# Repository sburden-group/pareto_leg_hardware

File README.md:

# Pareto Leg Hardware

contains all hardware (and control software) designs for the Pareto Leg

## Setup
Getting your environment ready to talk to some robot legs will involve:
1. provisioning your computer
1. provisioning the ODrive with the right firmware
1. calibrating the ODrive motors
1. Assembling the leg hardware
1. Wiring the leg electronics
1. Setting the zero point for each leg element

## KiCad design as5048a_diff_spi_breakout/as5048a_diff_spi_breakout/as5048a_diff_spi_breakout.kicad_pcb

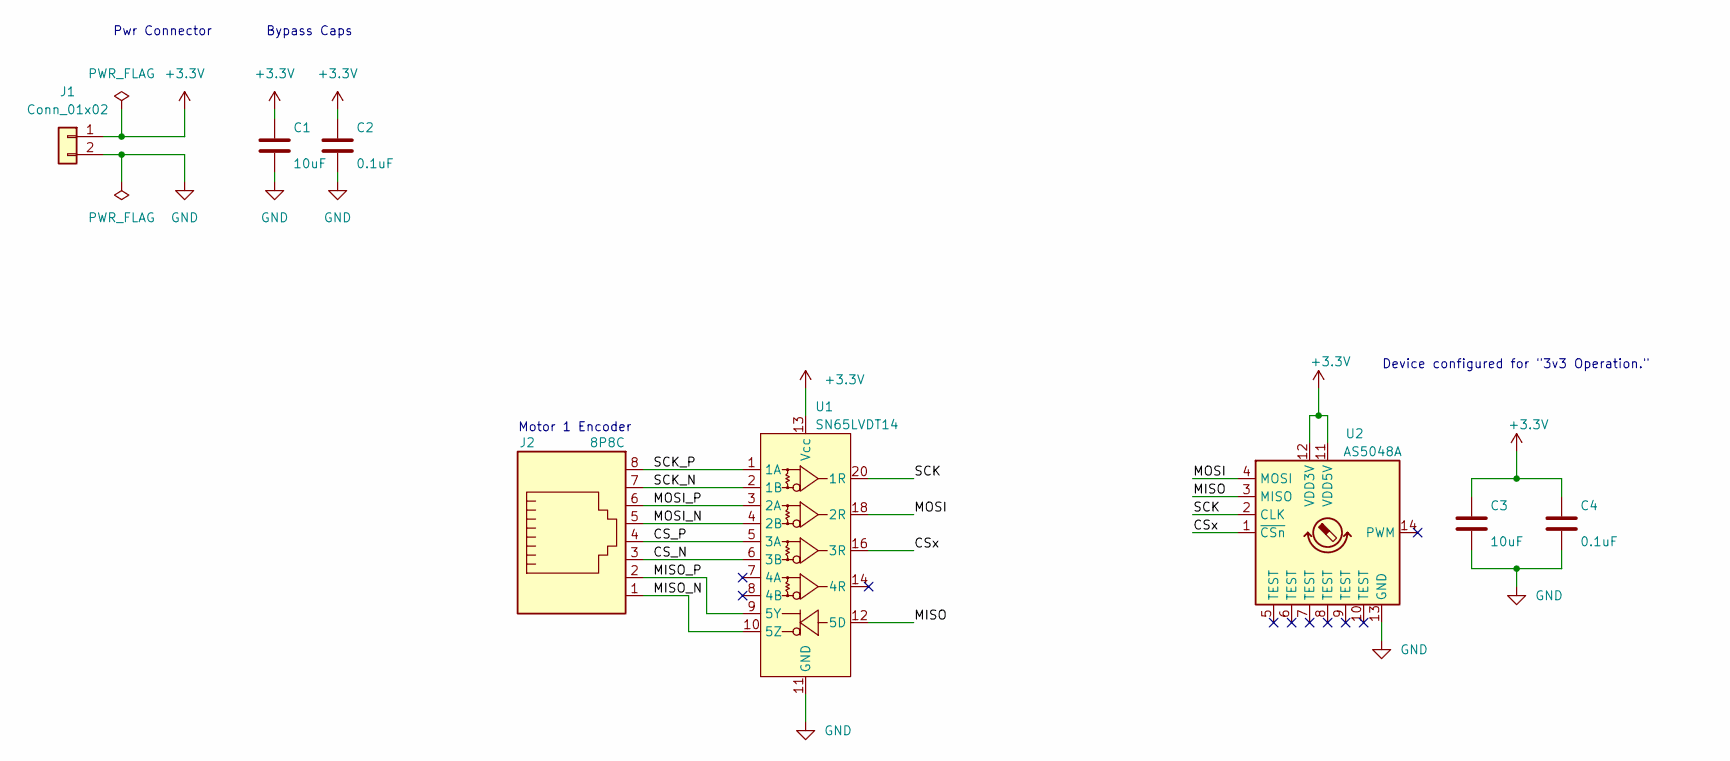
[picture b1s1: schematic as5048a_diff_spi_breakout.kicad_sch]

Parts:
C1, C3: 10uF; C_0603_1608Metric_Pad1.05x0.95mm_HandSolder
C2, C4: 0.1uF; C_0603_1608Metric_Pad1.05x0.95mm_HandSolder
J1: Conn_01x02; Molex_Micro-Fit_3.0_43650-0212_1x02_P3.00mm
J2: 8P8C; RJ45_Amphenol_SMD_RJSSE-5080-01T
U1: SN65LVDT14; TSSOP-20_4.4x6.5mm_P0.65mm
U2: AS5048A; TSSOP-14_4.4x5mm_P0.65mm

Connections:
+3V3: C1.1, C2.1, C3.1, C4.1, J1.1, U1.13 (Vcc), U1.17 (Vcc), U2.11 (VDD5V), U2.12 (VDD3V)
/CS_N: J2.3, U1.6 (3B)
/CS_P: J2.4, U1.5 (3A)
/CSx: U1.16 (3R), U2.1 (~CSn)
/MISO: U1.12 (5D), U2.3 (MISO)
/MISO_N: J2.1, U1.10 (5Z)
/MISO_P: J2.2, U1.9 (5Y)
/MOSI: U1.18 (2R), U2.4 (MOSI)
/MOSI_N: J2.5, U1.4 (2B)
/MOSI_P: J2.6, U1.3 (2A)
/SCK: U1.20 (1R), U2.2 (CLK)
/SCK_N: J2.7, U1.2 (1B)
/SCK_P: J2.8, U1.1 (1A)
GND: C1.2, C2.2, C3.2, C4.2, J1.2, U1.11 (GND), U1.15 (GND), U1.19 (GND), U2.13 (GND)

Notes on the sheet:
Pwr Connector
Motor 1 Encoder
Bypass Caps
Device configured for "3v3 Operation."

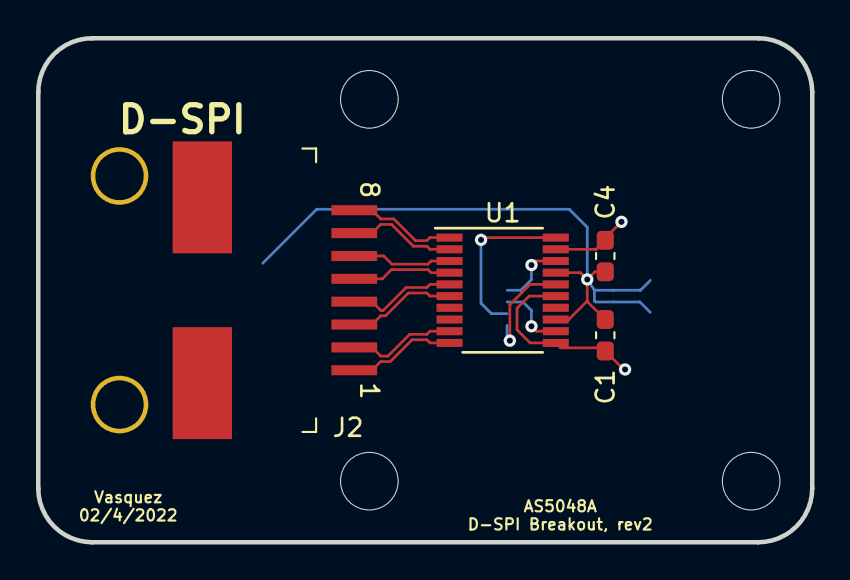
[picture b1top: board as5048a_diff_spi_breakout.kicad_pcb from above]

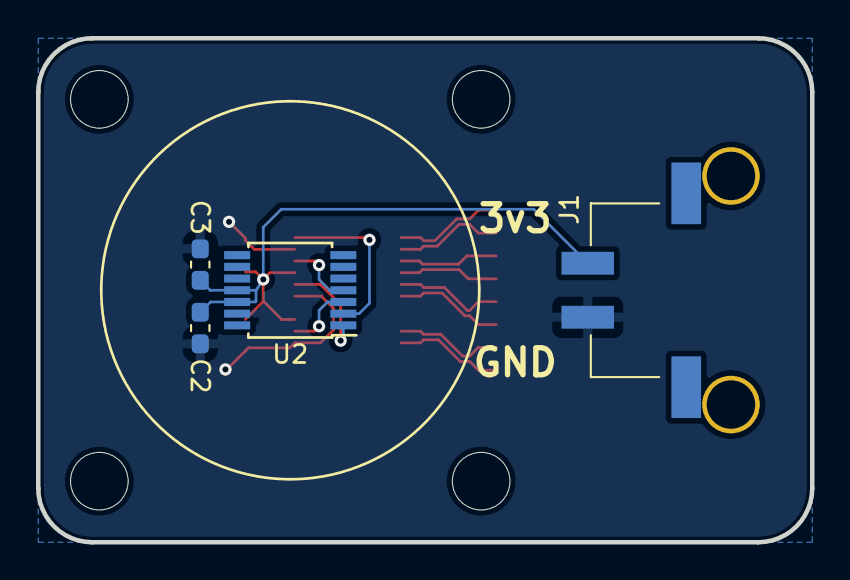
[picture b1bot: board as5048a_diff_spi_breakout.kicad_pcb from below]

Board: 2 copper layers, 43.0 x 28.0 mm, 8 parts (4 on the bottom side), 14 nets.

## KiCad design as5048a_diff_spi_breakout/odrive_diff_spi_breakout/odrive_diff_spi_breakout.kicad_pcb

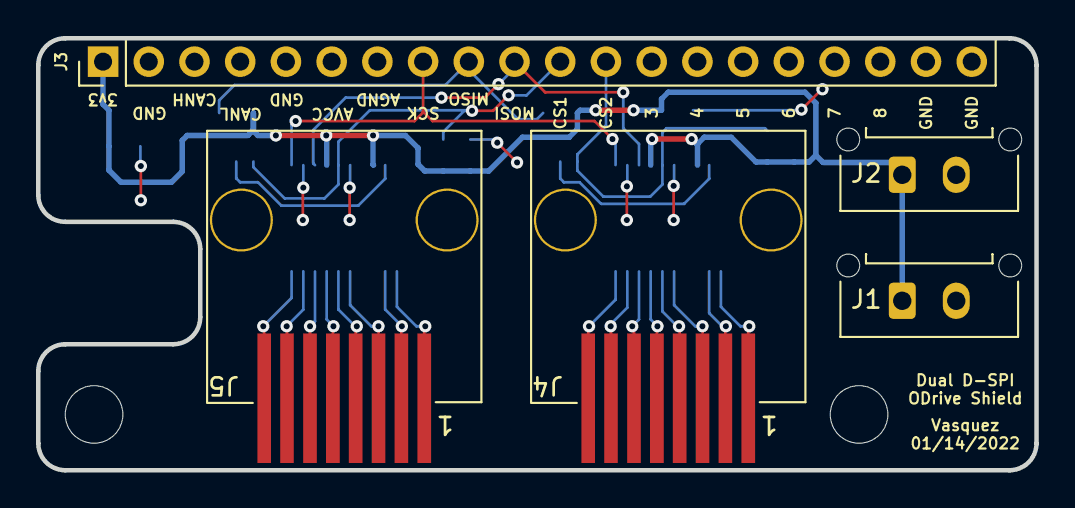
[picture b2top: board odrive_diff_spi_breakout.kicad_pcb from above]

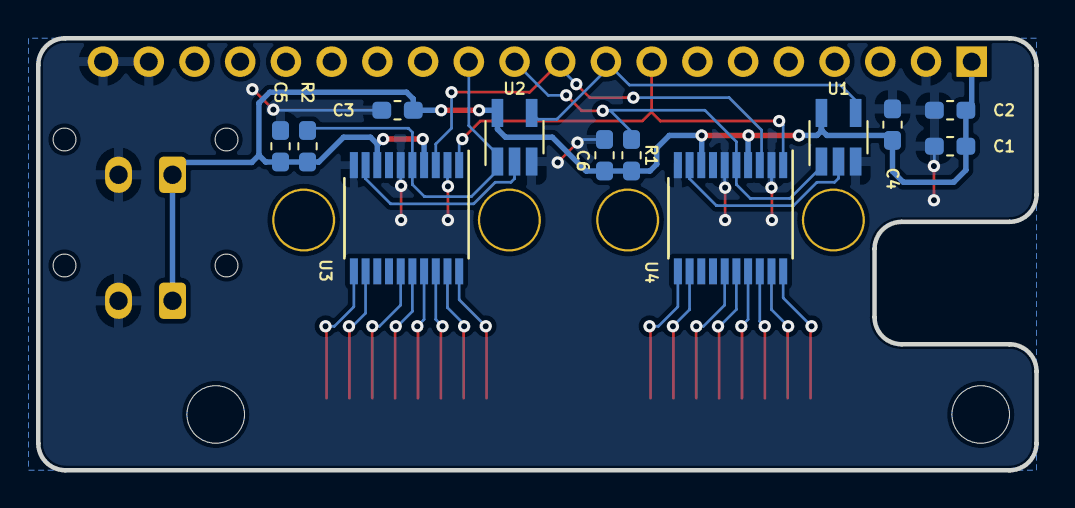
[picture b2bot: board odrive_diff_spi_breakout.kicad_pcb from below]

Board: 2 copper layers, 55.5 x 24.0 mm, 17 parts (12 on the bottom side), 25 nets.

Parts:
C1: 10uF; C_0603_1608Metric_Pad1.05x0.95mm_HandSolder
C2, C3, C4: 0.1uF; C_0603_1608Metric_Pad1.05x0.95mm_HandSolder
C5, C6: 1uF; C_0603_1608Metric_Pad1.05x0.95mm_HandSolder
J1, J2: Conn_01x02; Molex_Micro-Fit_3.0_43650-0215_1x02_P3.00mm_Vertical
J3: Conn_01x20; PinHeader_1x20_P2.54mm_Vertical
J4, J5: 8P8C; RJ45_Molex_SMD_0955036891
R1, R2: 4k7; R_0603_1608Metric_Pad1.05x0.95mm_HandSolder
U1, U2: 74CBTLV1G125; SOT-23-5_HandSoldering
U3, U4: SN65LVDT41; TSSOP-20_4.4x6.5mm_P0.65mm

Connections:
+3V3: C1.1, C2.1, C3.1, C4.1, C5.1, C6.1, J1.1, J2.1, J3.1, R1.1, R2.1, U1.5 (VCC), U2.5 (VCC), U3.4 (Vcc), U3.8 (Vcc), U4.4 (Vcc), U4.8 (Vcc)
/CS1: J3.11, R1.2, U1.1 (~OE), U4.5 (3D)
/CS2: J3.12, R2.2, U2.1 (~OE), U3.5 (3D)
/MISO: J3.9, U1.4 (B), U2.4 (B)
/MISO1: U1.2 (A), U4.9 (5R)
/MISO2: U2.2 (A), U3.9 (5R)
/MOSI: J3.10, U3.3 (2D), U4.3 (2D)
/SCK: J3.8, U3.1 (1D), U4.1 (1D)
GND: C1.2, C2.2, C3.2, C4.2, C5.2, C6.2, J1.2, J2.2, J3.2, J3.5, J3.19, J3.20, U1.3 (GND), U2.3 (GND), U3.2 (GND), U3.6 (GND), U3.10 (GND), U4.2 (GND), U4.6 (GND), U4.10 (GND)
unnamed: J4.1, U3.11 (5B)
unnamed: J4.2, U3.12 (5A)
unnamed: J4.3, U3.15 (3Z)
unnamed: J4.4, U3.16 (3Y)
unnamed: J4.5, U3.17 (2Z)
unnamed: J4.6, U3.18 (2Y)
unnamed: J4.7, U3.19 (1Z)
unnamed: J4.8, U3.20 (1Y)
unnamed: J5.1, U4.11 (5B)
unnamed: J5.2, U4.12 (5A)
unnamed: J5.3, U4.15 (3Z)
unnamed: J5.4, U4.16 (3Y)
unnamed: J5.5, U4.17 (2Z)
unnamed: J5.6, U4.18 (2Y)
unnamed: J5.7, U4.19 (1Z)
unnamed: J5.8, U4.20 (1Y)

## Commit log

2022-01-14 adding skeleton bringup code
2022-01-23 rev1 of pcbs finished
2022-01-25 changes amber made
2022-01-26 motor configuration figured out
2022-01-28 updated tuning script
2022-01-28 config for one motor looks good
2022-02-09 adding pareto leg kins
2022-02-09 starting python control code
2022-02-10 fw kins tests work
2022-02-10 adding gitignore and working fw/inv kins
2022-02-10 folder re-org
2022-02-12 updating driver
2022-02-12 adding wrapper for class
2022-02-18 folder restructure
2022-02-18 writing motor script for provisioning two motors
2022-02-18 adding todos in the readme
2022-02-18 adding motor angle get/set funcs
2022-02-23 adding usb analog input streamer
2022-02-28 adding bringup script for commissioning a fresh leg
2022-03-01 directory reorg
2022-03-01 updating config script.
2022-03-02 adding install script
2022-03-03 adding pd controller demo
2022-03-08 demystifying timer update rate
2022-03-08 adding udev rules
2022-03-08 adding daq provisioning instructions
2022-03-09 updating readme
2022-03-09 adding readme with folder structure info
2022-03-09 adding example julia com setup
2022-03-09 updating julia example
2022-03-09 adding some print output for daq
2022-03-10 get_state works
2022-03-10 adding test file for reading motor angles.
2022-03-11 first benchtop tests
2022-03-11 pre merge commit
2022-03-11 tweaking bringup config
2022-03-14 updates to two lab experiments
2022-03-14 adding cad model
2022-03-15 adding oscilloscope script for sanity checking
2022-03-18 added pid_example.py
2022-03-22 Add files via upload
    adding knee assembly doc
2022-03-24 oodles of changes, including fixed wrapping my my_odd. TODO update all experiment scripts
2022-03-24 actually, still trying to fix the motor angle wrapping but. Experiment scripts are TODO
2022-03-24 updated example_julia_commpunication.py script to handle new motor calibration measurements
2022-03-29 adding configurations pic
2022-03-29 adding pics for editing sw files
2022-03-31 updating odrive branch
2022-03-31 updating motor bringup docs
2022-03-31 updating readmes
2022-04-01 adding stls in printing orientations
2022-04-01 adding print list
2022-04-07 joey pushing lots of software changes, most lab experiment scripts are still broken
2022-04-16 major changes to leg cad
2022-04-16 major rework of cad in progress
2022-05-01 working on experiment scripts
2022-05-02 update to solidworks design files for version 5 of pareto leg
2022-05-10 hopping experiment protocol implemented
2022-05-16 added new programs to lab_experiments for incremental testing of control software
2023-02-17 major update post summer 2022
